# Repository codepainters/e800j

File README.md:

# Elwro 800 Junior replica

This repository contains all the necessary files to build a replica of [Elwro 800 Junior](https://pl.wikipedia.org/wiki/Elwro_800_Junior), a Polish home computer that can be considered a  [ZX Spectrum](https://en.wikipedia.org/wiki/ZX_Spectrum) clone. As of May 5, 2025, there are 3 successful builds, so the design files can be assumed valid.

## PCBs

The replica consists of three separate PCBs:

* [e800j_rev_c](e800j_rev_c) is the main board, an exact clone of the original *Elwro 800 Junior Rev C* PCB.  The original dimensions and mounting holes have been precisely recreated, making it suitable as a direct replacement for damaged original boards. 
* [kbd_cherry](kbd_cherry) is a replacement keyboard that uses standard Cherry MX switches. I chose not to replicate the original keyboard, as its switches are nearly impossible to source.
* [ports_pcb](ports_pcb) is a ports breakout board designed to simplify connections and avoid the mess of individual wires. This board is optional, but if you choose to connect ports with wires (as in the original design), you’ll need to derive the connections from the schematics.

All boards were designed in KiCad 9. In addition to the KiCad project files, each directory includes Gerber files, an interactive BOM, and PDF schematics. Refer to the respective subdirectories for assembly instructions and details.

### Additional documentation

* [pinouts](docs/pinouts.md) of the connectors
* [scans](docs/scans/) of the original schematics and DTR (*dokumentacja techniczno-ruchowa* - Polish for *technical reference manual*)
* [SCART](docs/scart.md) cable schematics / discussion

## Side projects

* Several side projects were created alongside the main replica (hosted in separate repositories):
* [e800j_addr_dec_gal](https://github.com/codepainters/e800j_addr_dec_gal) - replacement for address decoder PROMs using `GAL16V8` (original `74S474` PROMs are hard to get)
* [e800j_addr_dec_atf](https://github.com/codepainters/e800j_addr_dec_atf) - SMT variant using `ATF1502ASL`
* [e800j_grafix](https://github.com/codepainters/e800j_grafix) - a small add-on board that fixes graphics glitches present in the original Elwro design
* [JuDIM](https://github.com/codepainters/judim) - Junior Disk Manager, a small CLI tool for transferring files to/from `DSK` images (similar in principle to [cpmtools](https://www.moria.de/~michael/cpmtools/))

More to follow.

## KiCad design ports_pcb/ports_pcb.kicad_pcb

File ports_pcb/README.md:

# Ports breakout PCB for the Elwro 800 Junior replica

The idea behind this board is to simplify building the Junior replica (and not only that; read the notes section below), by using PCB-mounted connectors and switches, thus avoiding all the messy wire connections, as done in the original *Elwro 800 Junior*:

## Files

This directory contains the KiCAD 9 project, plus:

* schematics in PDF format - [color](ports_pcb.pdf) and [b&w](ports_pcb_bw.pdf)
* interactive [BOM](ports_pcb_ibom.html) (you need to download the file and open it locally) 
* [Gerber](gerbers) files (JLCPCB-compatible)

## Assembly

It's best to follow the interactive [BOM](ports_pcb_ibom.html).

### Options

There are some choices to be made:

* the original *Elwro* expects the joystick to short pins 1, 2, 3, 4 and 6 to `+5V` (and not to `GND`, as is usually done). 
  Because of this, pin 8 of the joystick connector is connected to the `+5V` rail.

  I decided to add 5 simple inverters (each consisting of a PNP transistor and a resistor) to make the port more standards-compliant 
  (allowing auto-fire joysticks to work as expected). With this modification pin 8 is tied to `GND`, pin 7 delivers `+5V` (via 
   a 27-ohm resistor on the mainboard), and pins 1, 2, 3, 4 and 6 react to shorting to ground.

  * If you want to use my mod, you need to:

    * assemble `T1..T5` transistors and `R1..R5` resistors

    * short pins 1 and 2 of `JP1` 

  * If you want to be 100% compatible with the original *Junior* instead:

    * solder jumpers instead of `R1..R5` resistors

    * solder jumpers between pins 1 and 2 of `T1..T5`

    * short pins 2 and 3 of `JP1`

* if a SCART cable is used, it is necessary to pull SCART's pin 16 (aka *Fast Blank*) above 1V to switch 
  the TV set to RGB signal. Unfortunately, Junior's RGB connector doesn't include a power pin, and there 
  are no spare pins to use. 

  I decided to make pin 8 of the RGB connector configurable between `SYN_H` and `+5V`, as the `SYN_H` signal is not necessary
  for SCART operation. Similarly, `SYN_V` is not really needed, so I've added `JP3` jumper allowing for disconnecting
  pin 6 and using it for other purposes. Also, `JP4` jumper allows for disconnecting `FON` signal from pin 7 (there's a plan to use pins 6 and 7 for stereo audio from AY-3-8910/12 card).

  So, if you want to use a SCART cable, you most likely want to:

  * assemble `C1` capacitor
  * put a jumper in place of  `R6` (the initial idea was to put a 180-ohm resistor there to limit the fast blank current, but now I think it's better to put it in the cable itself)
  * short pins 1 and 2 of `JP2`

  For a detailed explanation of the SCART issues  (as well as the cable schematics) , see [here](../docs/scart.md).

### Board stacking

The ports breakout PCB is designed to be mounted below the *Junior* main board and secured in place with M3 bolts. Corresponding pads on both the ports and main PCBs have the same labels (`J1` on the ports board should be connected to `J1` on the main board, `J2` to `J2`, etc.) and are positioned above each other (with 4 exceptions, see below), so they can be connected either by soldering short vertical wires (e.g., cut resistor pins, allowing for 5 mm spacing between the PCBs), or using "gold pin" connectors (requiring ~10 mm spacing). 

Here's how the boards look stacked together:

Close-up of the connections:

There are the following exceptions that require short insulated wire connections (`J13` can be left unconnected):

* `J41` and `J42` - for the reset button
* `J11` and `J12` - `+5V` and `GND`, respectively

Close-up of the wire connections:

## Other Notes

Note that:

* *Elwro 800 Junior* uses a `DB37` connector for the printer, while my board uses the more common `DB25`. This saves a lot of space,
  and standard PC `DB25` printer cables are much easier to find.
* the fuse socket is optional, but I suggest using a fuse - better safe than sorry.

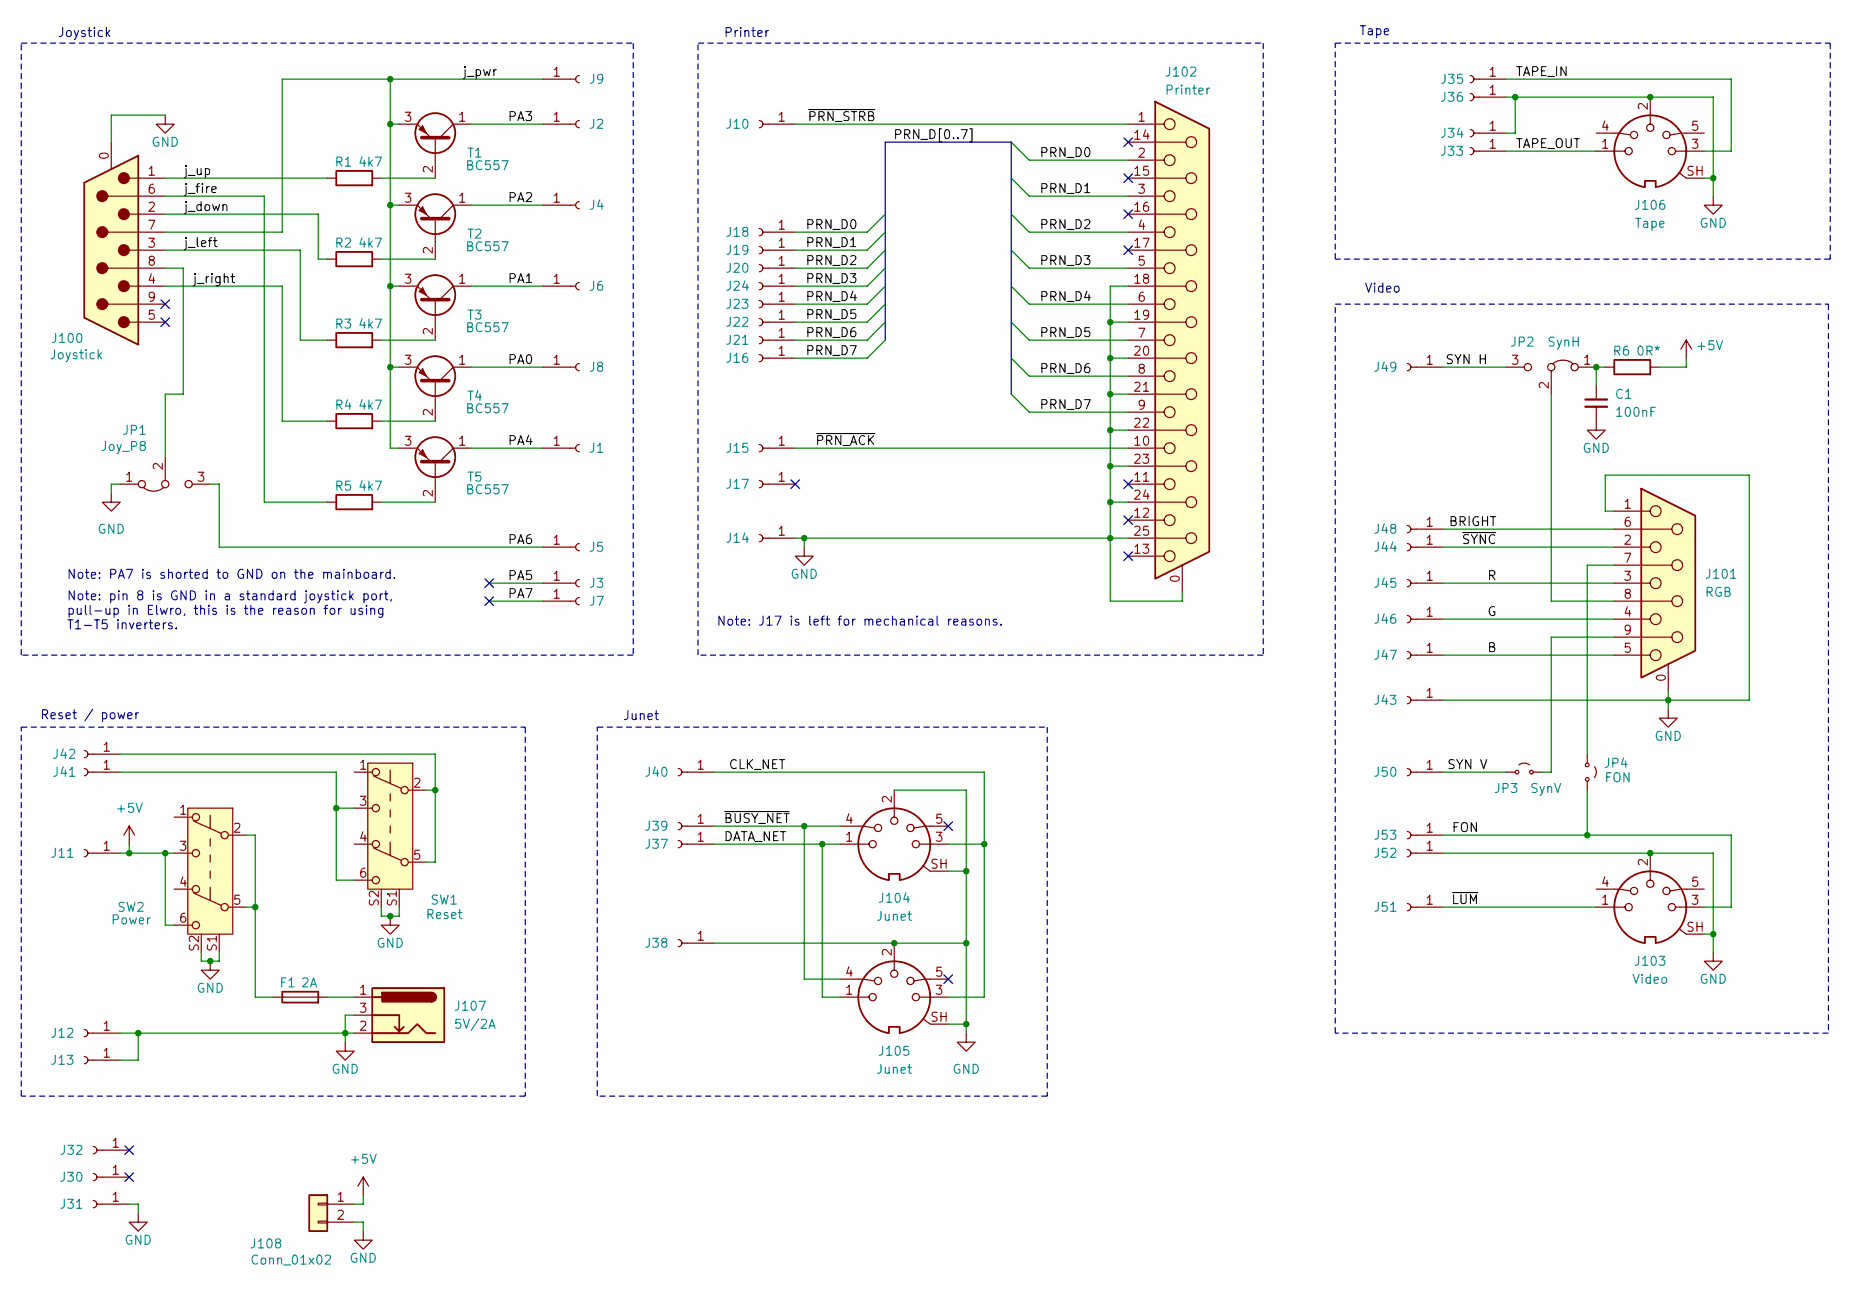
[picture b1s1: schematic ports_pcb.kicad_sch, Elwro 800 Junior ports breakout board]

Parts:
C1: 100nF; C_Disc_D5.0mm_W2.5mm_P2.50mm
F1: 2A; Fuseholder_Clip-5x20mm_Littelfuse_445-030_Inline_P20.50x5.2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
J1, J2, J3, J4, J5, J6, J7, J8, J9, J10, J14, J15, J16, J17, J18, J19, J20, J21, J22, J23, J24, J30, J31, J32, J33, J34, J35, J36, J43, J44, J45, J46, J47, J48, J49, J50, J51, J52, J53: Conn_01x01_Socket; PinHeader_1x01_P2.54mm_Vertical
J11, J12, J13: Conn_01x01_Socket; pin24
J37, J38, J39, J40: PinHeader_1x01_P2.54mm_Vertical
J41: RESET1; pin
J42: RESET2; pin
J100: Joystick; DSUB-9_Pins_Horizontal_P2.77x2.84mm_EdgePinOffset7.70mm_Hou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
J101: RGB; DSUB-9_Socket_Horizontal_P2.77x2.84mm_EdgePinOffset7.70mm_H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
J102: Printer; DSUB-25_Socket_Horizontal_P2.77x2.84mm_EdgePinOffset7.70mm_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
J103: Video; CUI_SDS-50J
J104, J105: Junet; CUI_SDS-50J
J106: Tape; CUI_SDS-50J
J107: 5V/2A; BarrelJack_GCT_DCJ200-10-A_Horizontal
J108: Conn_01x02; Molex_KK-254_AE-6410-02A_1x02_P2.54mm_Vertical
JP1: Joy_P8; PinHeader_1x03_P2.54mm_Vertical
JP2: SynH; PinHeader_1x03_P2.54mm_Vertical
JP3: SynV; PinHeader_1x02_P2.54mm_Vertical
JP4: FON; PinHeader_1x02_P2.54mm_Vertical
R1, R2, R3, R4, R5: 4k7; R_Axial_DIN0207_L6.3mm_D2.5mm_P10.16mm_Horizontal
R6: 0R*; R_Axial_DIN0207_L6.3mm_D2.5mm_P10.16mm_Horizontal
SW1: Reset; PS-22F03
SW2: Power; PS-22F03
T1, T2, T3, T4, T5: BC557; TO-92_Inline

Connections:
+5V: J11.1, J108.1, R6.2, SW2.3 (C), SW2.6 (C)
/B: J47.1, J101.5
/BRIGHT: J48.1, J101.6
/CLK_NET: J40.1, J104.3, J105.3
/DATA_NET: J37.1, J104.1, J105.1
/FON: J53.1, J103.3, JP4.1 (A)
/G: J46.1, J101.4
/PA0: J8.1, T4.1 (C)
/PA1: J6.1, T3.1 (C)
/PA2: J4.1, T2.1 (C)
/PA3: J2.1, T1.1 (C)
/PA4: J1.1, T5.1 (C)
/PA5: J3.1
/PA6: J5.1, JP1.3 (B)
/PA7: J7.1
/PRN_D0: J18.1, J102.2
/PRN_D1: J19.1, J102.3
/PRN_D2: J20.1, J102.4
/PRN_D3: J24.1, J102.5
/PRN_D4: J23.1, J102.6
/PRN_D5: J22.1, J102.7
/PRN_D6: J21.1, J102.8
/PRN_D7: J16.1, J102.9
/R: J45.1, J101.3
/SYN H: J49.1, JP2.3 (B)
/SYN V: J50.1, JP3.2 (B)
/TAPE_IN: J35.1, J106.3
/TAPE_OUT: J33.1, J106.1
/j_down: J100.2, R2.1
/j_fire: J100.6, R5.1
/j_left: J100.3, R3.1
/j_pwr: J9.1, J100.7, T1.3 (E), T2.3 (E), T3.3 (E), T4.3 (E), T5.3 (E)
/j_right: J100.4, R4.1
/j_up: J100.1, R1.1
/~BUSY_NET: J39.1, J104.4, J105.4
/~LUM: J51.1, J103.1
/~PRN_ACK: J15.1, J102.10
/~PRN_STRB: J10.1, J102.1
/~SYNC: J44.1, J101.2
GND: C1.2, J12.1, J13.1, J14.1, J31.1, J34.1, J36.1, J38.1, J43.1, J52.1, J100.0 (PAD), J101.0 (PAD), J101.1, J102.0 (PAD), J102.18, J102.19, J102.20, J102.21, J102.22, J102.23, J102.24, J102.25, J103.2, J103.SH, J104.2, J104.SH, J105.2, J105.SH, J106.2, J106.SH, J107.2, J107.3, J108.2, JP1.1 (A), SW1.S1, SW1.S2, SW2.S1, SW2.S2
unnamed: F1.1, SW2.2 (B), SW2.5 (B)
unnamed: F1.2, J107.1
unnamed: J41.1, SW1.3 (C), SW1.6 (C)
unnamed: J42.1, SW1.2 (B), SW1.5 (B)
unnamed: J100.8, JP1.2 (C)
unnamed: C1.1, JP2.1 (A), R6.1
unnamed: J101.8, JP2.2 (C)
unnamed: J101.9, JP3.1 (A)
unnamed: J101.7, JP4.2 (B)
unnamed: R1.2, T1.2 (B)
unnamed: R2.2, T2.2 (B)
unnamed: R3.2, T3.2 (B)
unnamed: R4.2, T4.2 (B)
unnamed: R5.2, T5.2 (B)

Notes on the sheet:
Printer
Note: pin 8 is GND in a standard joystick port, pull-up in Elwro, this is the reason for using T1-T5 inverters.
Tape
Junet
Video
Note: J17 is left for mechanical reasons.
Reset / power
Note: PA7 is shorted to GND on the mainboard.
Joystick

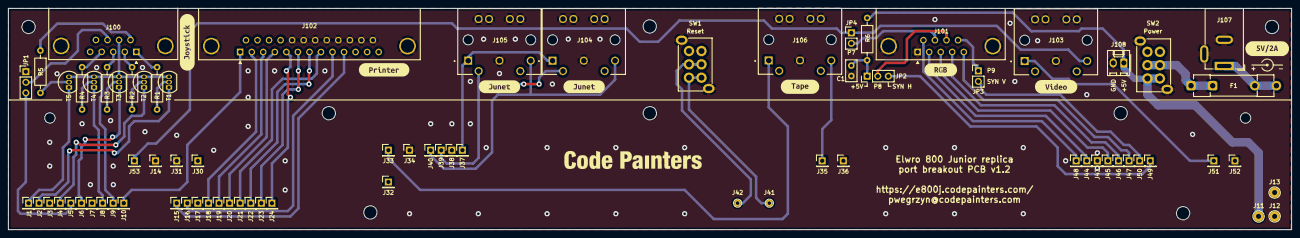
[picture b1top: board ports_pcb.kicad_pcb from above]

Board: 2 copper layers, 308.0 x 53.1 mm, 92 parts (0 on the bottom side), 52 nets.

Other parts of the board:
IMG1: logo
MH1, MH5: mth25
MH2, MH3, MH4, MH6, MH7: mth32
kibuzzard-67F8F98E: G***; kibuzzard-67F8F98E
kibuzzard-67F911BA: G***; kibuzzard-67F911BA
kibuzzard-67F911F0, kibuzzard-67F911F0#2: G***; kibuzzard-67F911F0
kibuzzard-67F9119B: G***; kibuzzard-67F9119B
kibuzzard-67F91269: G***; kibuzzard-67F91269
kibuzzard-67F91296: G***; kibuzzard-67F91296
kibuzzard-67F91771: G***; kibuzzard-67F91771

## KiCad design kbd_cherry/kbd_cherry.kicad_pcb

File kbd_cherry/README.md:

# Keyboard with Cherry MX switches

Note:

* this PCB is **not a replacement** for the original keyboard PCB. The intention here was to create a keyboard for the replica, and not for restoration work. Original switches are nearly impossible to find, so there is little point in replicating the original board anyway.
* that said, the 10-pin connectors match the original pinout, so this PCB can be connected to the original PCB, for example for testing purposes.

* https://www.keyboard-layout-editor.com/ was used to create the layout. I decided to follow the keycap widths of the original keyboard which are slightly different from a typical PC keyboard (e.g., the  `TAB` key is only `1U` wide). There are many other differences, custom keycap labels are necessary anyway, so it doesn't bother me too much. 
* the spacebar requires a typical Cherry stabilizer to work properly (the PCB-mount variant). There are stabilizer holes around the `Up` and `Down` cursor keys as well, but that’s due to the footprint used, these keys don't actually need stabilizers.

This directory contains KiCAD 9 project, plus:

* schematics in PDF format - [color](kbd_cherry.pdf) and [b&w](kbd_cherry_bw.pdf)
* [keyboard-layout.json](docs/keyboard-layout.json) file for the https://www.keyboard-layout-editor.com/
* [layout](docs/keyboard-layout.png) diagram
* relevant [scans](docs/dtr) from the original Elwro documentation
* [Gerber](gerbers) files

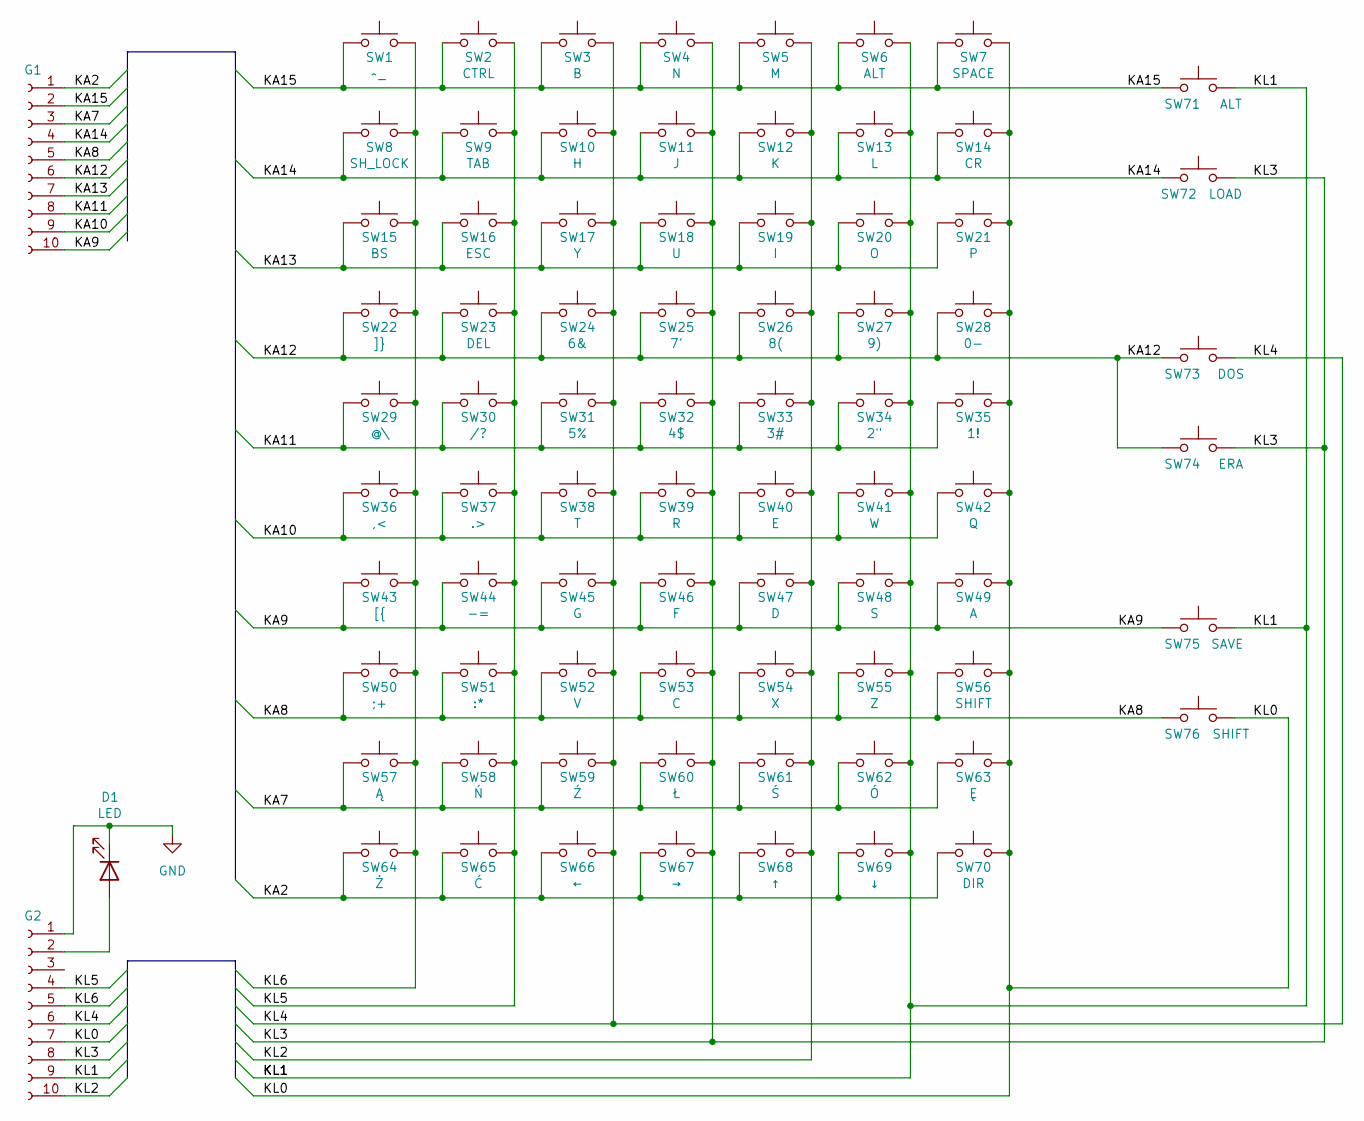
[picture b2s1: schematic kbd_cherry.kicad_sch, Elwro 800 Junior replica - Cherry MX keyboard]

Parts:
D1: LED; LED_D5.0mm
G1, G2: Conn_01x10_Socket; PinHeader_1x10_P2.54mm_Vertical
SW1: ^-; SW_Cherry_MX_1.00u_PCB
SW2: CTRL; SW_Cherry_MX_1.00u_PCB
SW3: B; SW_Cherry_MX_1.00u_PCB
SW4: N; SW_Cherry_MX_1.00u_PCB
SW5: M; SW_Cherry_MX_1.00u_PCB
SW6, SW71: ALT; SW_Cherry_MX_1.00u_PCB
SW7: SPACE; SW_Cherry_MX_6.25u_PCB
SW8: SH_LOCK; SW_Cherry_MX_1.00u_PCB
SW9: TAB; SW_Cherry_MX_1.00u_PCB
SW10: H; SW_Cherry_MX_1.00u_PCB
SW11: J; SW_Cherry_MX_1.00u_PCB
SW12: K; SW_Cherry_MX_1.00u_PCB
SW13: L; SW_Cherry_MX_1.00u_PCB
SW14: CR; SW_Cherry_MX_1.50u_PCB
SW15: BS; SW_Cherry_MX_1.00u_PCB
SW16: ESC; SW_Cherry_MX_1.00u_PCB
SW17: Y; SW_Cherry_MX_1.00u_PCB
SW18: U; SW_Cherry_MX_1.00u_PCB
SW19: I; SW_Cherry_MX_1.00u_PCB
SW20: O; SW_Cherry_MX_1.00u_PCB
SW21: P; SW_Cherry_MX_1.00u_PCB
SW22: ]}; SW_Cherry_MX_1.00u_PCB
SW23: DEL; SW_Cherry_MX_1.00u_PCB
SW24: 6&; SW_Cherry_MX_1.00u_PCB
SW25: 7'; SW_Cherry_MX_1.00u_PCB
SW26: 8(; SW_Cherry_MX_1.00u_PCB
SW27: 9); SW_Cherry_MX_1.00u_PCB
SW28: 0-; SW_Cherry_MX_1.00u_PCB
SW29: @\; SW_Cherry_MX_1.00u_PCB
SW30: /?; SW_Cherry_MX_1.00u_PCB
SW31: 5%; SW_Cherry_MX_1.00u_PCB
SW32: 4$; SW_Cherry_MX_1.00u_PCB
SW33: 3#; SW_Cherry_MX_1.00u_PCB
SW34: 2"; SW_Cherry_MX_1.00u_PCB
SW35: 1!; SW_Cherry_MX_1.00u_PCB
SW36: ,<; SW_Cherry_MX_1.00u_PCB
SW37: .>; SW_Cherry_MX_1.00u_PCB
SW38: T; SW_Cherry_MX_1.00u_PCB
SW39: R; SW_Cherry_MX_1.00u_PCB
SW40: E; SW_Cherry_MX_1.00u_PCB
SW41: W; SW_Cherry_MX_1.00u_PCB
SW42: Q; SW_Cherry_MX_1.00u_PCB
SW43: [{; SW_Cherry_MX_1.00u_PCB
SW44: -=; SW_Cherry_MX_1.00u_PCB
SW45: G; SW_Cherry_MX_1.00u_PCB
SW46: F; SW_Cherry_MX_1.00u_PCB
SW47: D; SW_Cherry_MX_1.00u_PCB
SW48: S; SW_Cherry_MX_1.00u_PCB
SW49: A; SW_Cherry_MX_1.00u_PCB
SW50: ;+; SW_Cherry_MX_1.00u_PCB
SW51: :*; SW_Cherry_MX_1.00u_PCB
SW52: V; SW_Cherry_MX_1.00u_PCB
SW53: C; SW_Cherry_MX_1.00u_PCB
SW54: X; SW_Cherry_MX_1.00u_PCB
SW55: Z; SW_Cherry_MX_1.00u_PCB
SW56: SHIFT; SW_Cherry_MX_1.00u_PCB
SW57: Ą; SW_Cherry_MX_1.00u_PCB
SW58: Ń; SW_Cherry_MX_1.00u_PCB
SW59: Ź; SW_Cherry_MX_1.00u_PCB
SW60: Ł; SW_Cherry_MX_1.00u_PCB
SW61: Ś; SW_Cherry_MX_1.00u_PCB
SW62: Ó; SW_Cherry_MX_1.00u_PCB
SW63: Ę; SW_Cherry_MX_1.00u_PCB
SW64: Ż; SW_Cherry_MX_1.00u_PCB
SW65: Ć; SW_Cherry_MX_1.00u_PCB
SW66: ←; SW_Cherry_MX_1.00u_PCB
SW67: →; SW_Cherry_MX_1.00u_PCB
SW68: ↑; SW_Cherry_MX_2.00u_PCB
SW69: ↓; SW_Cherry_MX_2.00u_PCB
SW70: DIR; SW_Cherry_MX_1.00u_PCB
SW72: LOAD; SW_Cherry_MX_1.00u_PCB
SW73: DOS; SW_Cherry_MX_1.00u_PCB
SW74: ERA; SW_Cherry_MX_1.00u_PCB
SW75: SAVE; SW_Cherry_MX_1.00u_PCB
SW76: SHIFT; SW_Cherry_MX_1.50u_PCB

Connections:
/KA2: G1.1, SW64.1, SW65.1, SW66.1, SW67.1, SW68.1, SW69.1, SW70.2
/KA7: G1.3, SW57.1, SW58.1, SW59.1, SW60.1, SW61.1, SW62.1, SW63.1
/KA8: G1.5, SW50.1, SW51.1, SW52.1, SW53.1, SW54.1, SW55.1, SW56.1, SW76.1
/KA9: G1.10, SW43.1, SW44.1, SW45.1, SW46.1, SW47.1, SW48.1, SW49.1, SW75.2
/KA10: G1.9, SW36.1, SW37.1, SW38.1, SW39.1, SW40.1, SW41.1, SW42.1
/KA11: G1.8, SW29.1, SW30.1, SW31.1, SW32.1, SW33.1, SW34.1, SW35.1
/KA12: G1.6, SW22.1, SW23.1, SW24.1, SW25.1, SW26.1, SW27.1, SW28.1, SW73.1, SW74.1
/KA13: G1.7, SW15.1, SW16.1, SW17.1, SW18.1, SW19.1, SW20.1, SW21.1
/KA14: G1.4, SW8.1, SW9.1, SW10.1, SW11.1, SW12.1, SW13.1, SW14.2, SW72.2
/KA15: G1.2, SW1.1, SW2.1, SW3.1, SW4.1, SW5.1, SW6.1, SW7.1, SW71.1
/KL0: G2.7, SW7.2, SW14.1, SW21.2, SW28.2, SW35.2, SW42.2, SW49.2, SW56.2, SW63.2, SW70.1, SW76.2
/KL1: G2.9, SW6.2, SW13.2, SW20.2, SW27.2, SW34.2, SW41.2, SW48.2, SW55.2, SW62.2, SW69.2, SW71.2, SW75.1
/KL2: G2.10, SW5.2, SW12.2, SW19.2, SW26.2, SW33.2, SW40.2, SW47.2, SW54.2, SW61.2, SW68.2
/KL3: G2.8, SW4.2, SW11.2, SW18.2, SW25.2, SW32.2, SW39.2, SW46.2, SW53.2, SW60.2, SW67.2, SW72.1, SW74.2
/KL4: G2.6, SW3.2, SW10.2, SW17.2, SW24.2, SW31.2, SW38.2, SW45.2, SW52.2, SW59.2, SW66.2, SW73.2
/KL5: G2.4, SW2.2, SW9.2, SW16.2, SW23.2, SW30.2, SW37.2, SW44.2, SW51.2, SW58.2, SW65.2
/KL6: G2.5, SW1.2, SW8.2, SW15.2, SW22.2, SW29.2, SW36.2, SW43.2, SW50.2, SW57.2, SW64.2
GND: D1.1 (K), G2.1
unnamed: D1.2 (A), G2.2

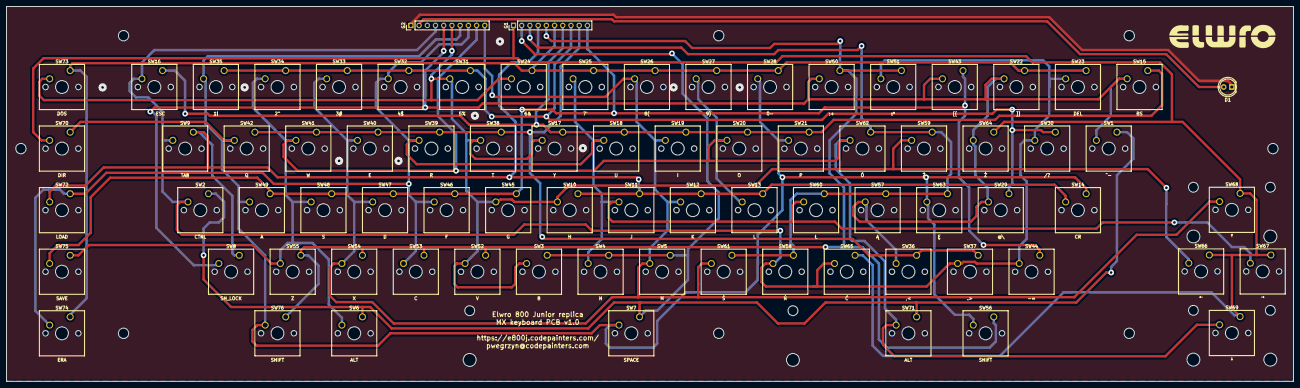
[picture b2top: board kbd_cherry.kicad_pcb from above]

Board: 2 copper layers, 398.1 x 116.0 mm, 87 parts (0 on the bottom side), 19 nets.

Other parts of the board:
MH1, MH2, MH3, MH4, MH5, MH6, MH7, MH8: MountingHole_3.2mm_M3_DIN965

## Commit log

2025-04-07 Imported ports_pcb v1.0
2025-04-07 Imported keyboard v1.0
2025-04-07 Mainboard rev C 1.0 imported
2025-04-07 Let's keep previous name.
2025-04-09 ports_pcb: converted to KiCAD 9, fixed 3d models (#1)
2025-04-09 Ports PCB: reworked joy (#8) and video (#10)
2025-04-11 ports_pcb: added fuse, aux power connector, changed DIN 3d model
2025-04-11 ports_pcb: schamtics in PDF files
2025-04-11 ports_pcb: fixed a typo in schematic title
2025-04-11 ports_pcb: labels replaced with thicker font (#11)
2025-04-12 ports_pcb: not sure why, but KiCAD added fon thickness everywhere
2025-04-12 ports_pcb: ibom config + html
2025-04-12 Reworking keyboard directory
2025-04-12 kbd_cherry: converted to KiCAD 9, schematic size reduced to A4
2025-04-12 kbd_cherry: schematics as PDFs
2025-04-13 ports_pcb: excluded Jx headers from BOM
2025-04-13 kbd_cherry: switched to local 3d models
2025-04-16 mainboard: converted to KiCAD9, vendored 3d models
2025-04-16 mainboard: get rid of external font references
2025-04-16 mainboard: schematics updated to v9.0
2025-04-17 ports_pcb: gerbers v1.1
2025-04-17 Moving gerbers - let's keep the dir-per-pcb scheme
2025-04-18 mainboard: CKPIX/rework via untented, other fixes (#5, #2)
2025-04-18 mianboard: more fixes (#3, #4, #6)
    - #3 - fixed GWP10 (keyboard connector) footprint pitch
    - #4 - increased Z3 jumper hole diameters
    - #6 - increased silkscreen circles diameter and thickness
2025-04-18 mainboard: post-chages clearance issues fixed
2025-04-18 mainboard: minor fixes
2025-04-18 mainboard: bom updated
2025-04-18 mainboard: gerber files
2025-05-06 READMEs and other docs
2025-05-06 Pinouts added
2025-05-06 Minor edit
2025-05-07 pngs with transparent background fixed
2025-05-07 PNG margins
2025-05-19 ports_pcb: added jP4 jumper to allow disconnecting FON (#13)
2025-05-19 prots_pcb: minor tweaks, v1.2
2025-05-19 ports_pcb: schematics + README update for 1.2
2025-05-19 DRC exclusions
    - fiducial collision with GND track (as on original board)
    - workaround for KiCad bug (net with &lt; or &gt; in name casuses false DRC alarm)
2025-06-06 UniFDC BOOT ROM
2025-07-21 Marked unpopulated components properly (see #14)
2025-08-21 Adding some assembler tests (color bars)
2025-08-29 README file for tests
2025-09-24 Test added: 02_color_bars2
